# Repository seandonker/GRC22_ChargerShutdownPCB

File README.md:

# GRC22 Charging Shutdown Board for Guelph's FSAE Club
This board lies inside the external charging enclosure and is responsible for processing certain safety signals.
It then determines if it is safe to activate the battery charger or not. 

**Schematic Theory**<br>
The board takes in three main safety signals: IMD Error, AMS Safety, and Charger Safety. IMD Error indicates the insulation in between the cells of the battery pack 
and the signal faults low when an error is detected. AMS Safety faults low as well when there is an issue with the voltage/temperature/current of any individual cell bank in the battery. Finally, 
charger safety sinks current when no error is present and is allowed to float when an error occurs. The latching logic is the core design challenge of this board. 
The FSAE rulebook has specific descriptions relating to the IMD and AMS signals as once an error is noticed, the output of the board must stay in the error state until 
manually reset (power cycled). This is why latches are required to save the error state. Two RS latches were implemented in combination with RC filters, AND gates, and inverters.
This was done to combat unknown input signal conditions on startup. A full input/output-state circuit trace can be seen in the provided files (ShutdownBoard_Latching_Logic_States).
The relay logic section acts as a chain of switches, so only if  the charge sink, IMD, AMS, E-stop, and interconnect states are all correct, will then the charger and accessories be provided power.

**Board Layout**<br>
The main requirement for the PCB layout was to be able to manufacture on a two layer PCB for cost reasons. The criteria for design were ease of assembly, connector and fuse access,
and the visibility of the indicator LEDs and silkscreen.

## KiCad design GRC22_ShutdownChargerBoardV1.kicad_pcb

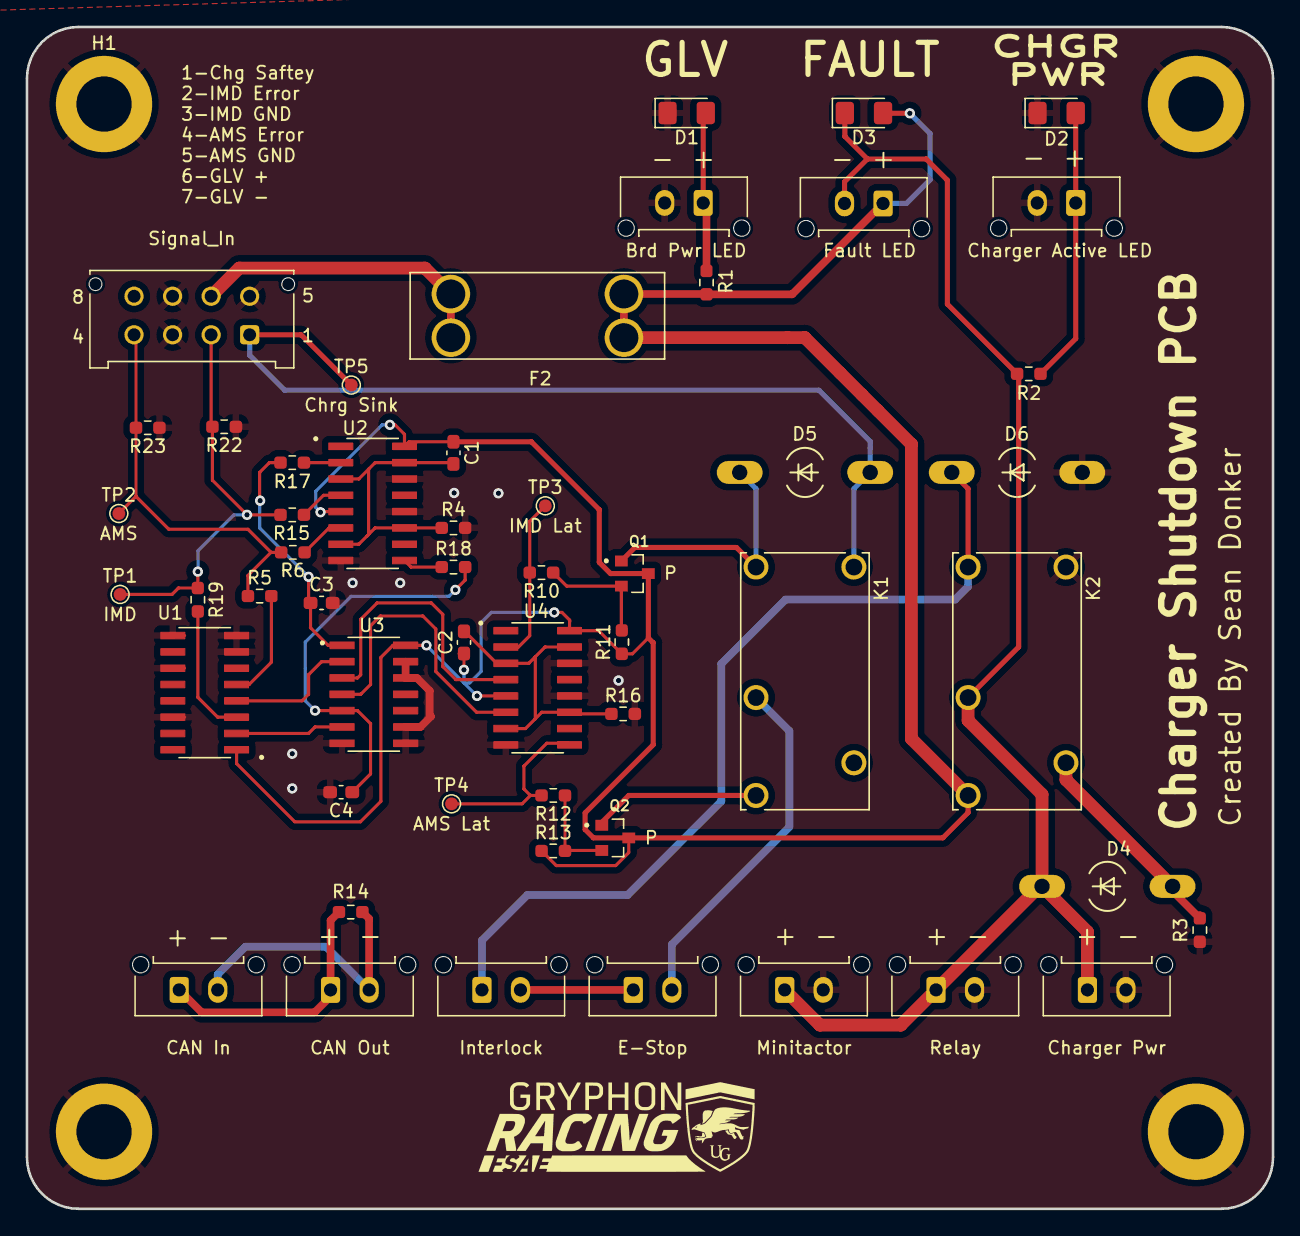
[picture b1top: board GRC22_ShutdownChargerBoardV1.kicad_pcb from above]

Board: 2 copper layers, 97.0 x 92.0 mm, 57 parts (0 on the bottom side), 35 nets.

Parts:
C1, C2: 100nF; C_0603_1608Metric_Pad1.08x0.95mm_HandSolder
C3, C4: .47nF; C_0603_1608Metric_Pad1.08x0.95mm_HandSolder
D1, D2, D3: LED; LED_1206_3216Metric_Pad1.42x1.75mm_HandSolder
D4, D5, D6: D; SOD57-10
F2: Fuse; FUSE_3557-2
H1, H2, H3, H4: M4_Hole; MountingHole_4.3mm_M4_DIN965_Pad
J1: Signal_In; Molex_Micro-Fit_3.0_43045-0812_2x04_P3.00mm_Vertical
J2: Charger Pwr; Molex_Micro-Fit_3.0_43650-0215_1x02_P3.00mm_Vertical
J3: Relay; Molex_Micro-Fit_3.0_43650-0215_1x02_P3.00mm_Vertical
J4: Minitactor; Molex_Micro-Fit_3.0_43650-0215_1x02_P3.00mm_Vertical
J5: Interlock; Molex_Micro-Fit_3.0_43650-0215_1x02_P3.00mm_Vertical
J6: E-Stop; Molex_Micro-Fit_3.0_43650-0215_1x02_P3.00mm_Vertical
J7: CAN In; Molex_Micro-Fit_3.0_43650-0215_1x02_P3.00mm_Vertical
J8: CAN Out; Molex_Micro-Fit_3.0_43650-0215_1x02_P3.00mm_Vertical
J9: Brd Pwr LED; Molex_Micro-Fit_3.0_43650-0215_1x02_P3.00mm_Vertical
J10: Charger Active LED; Molex_Micro-Fit_3.0_43650-0215_1x02_P3.00mm_Vertical
J11: Fault LED; Molex_Micro-Fit_3.0_43650-0215_1x02_P3.00mm_Vertical
K1, K2: ALQ112; RELAY_ALQ112
Q1, Q2: PMOS; RSC002
R1, R2, R3, R5, R6, R10, R12, R15, R19: 470; R_0603_1608Metric_Pad0.98x0.95mm_HandSolder
R4, R16: 1K; R_0603_1608Metric_Pad0.98x0.95mm_HandSolder
R11, R13: 100k; R_0603_1608Metric_Pad0.98x0.95mm_HandSolder
R14: 120; R_0603_1608Metric_Pad0.98x0.95mm_HandSolder
R17, R18: 10k; R_0603_1608Metric_Pad0.98x0.95mm_HandSolder
R22, R23: 2.2K; R_0603_1608Metric_Pad0.98x0.95mm_HandSolder
TP1: IMD; TestPoint_Pad_D1.0mm
TP2: AMS; TestPoint_Pad_D1.0mm
TP3: IMD Lat; TestPoint_Pad_D1.0mm
TP4: AMS Lat; TestPoint_Pad_D1.0mm
TP5: Chrg Sink; TestPoint_Pad_D1.0mm
U1: SOIC127P600X175-16N
U2, U4: MC14043BDG; SOIC127P600X175-16N
U3: MC14081BDG; SOIC127P600X175-14N

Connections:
+12V: C1.1, C2.1, D3.2 (A), F2.2, J11.1, K2.5, Q1.3 (S), Q2.3 (S), R1.1, R11.1, R13.1, U1.1 (VDD), U2.5 (E), U2.16 (VDD), U3.14 (VDD), U4.5 (E), U4.16 (VDD)
AMS GND: C3.2, C4.2, D1.1 (K), D2.1 (K), D6.2 (A), H1.1, H2.1, H3.1, H4.1, J1.3, J1.5, J1.7, J2.2, J3.2, J4.2, J9.2, J10.2, K2.2, R3.2, R4.2, R16.2, R22.1, R23.1, U1.7 (IN_c), U1.8 (VSS), U1.9 (IN_d), U1.11 (IN_e), U1.14 (IN_f), U2.8 (VSS), U2.12 (S2), U2.14 (S3), U3.7 (VSS), U3.8 (IN_1C), U3.9 (IN_2C), U3.12 (IN_1D), U3.13 (IN_2D), U4.8 (VSS), U4.12 (S2), U4.14 (S3)
AMS Saftey: J1.4, R5.1, R6.1, R23.2, TP2.1
AMS_Latched: R12.2, TP4.1, U4.9 (Q1)
CAN +: J7.1, J8.1, R14.2
CAN -: J7.2, J8.2, R14.1
Charger Pwr: D3.1 (K), D4.1 (K), J2.1, J3.1, J4.1, J11.2, K2.3, R2.1
Chg Saftey: D5.2 (A), J1.1, K1.2, TP5.1
E-Stop Out: J6.2, K1.3
E-Stop Rtn: J5.2, J6.1
GLV +: F2.1, J1.6
IMD Error: J1.2, R15.1, R19.1, R22.2, TP1.1
IMD_Latched: R10.2, TP3.1, U4.2 (Q0)
Interlock Rtn: D6.1 (K), J5.1, K2.1
unnamed: D1.2 (A), J9.1, R1.2
unnamed: D2.2 (A), J10.1, R2.2
unnamed: D4.2 (A), K2.4, R3.1
unnamed: D5.1 (K), K1.1, Q1.1 (D)
unnamed: Q1.2 (G), R10.1, R11.2
unnamed: K1.5, Q2.1 (D)
unnamed: Q2.2 (G), R12.1, R13.2
unnamed: R19.2, U1.3 (IN_a)
unnamed: R5.2, U1.5 (IN_b)
unnamed: U1.2 (OUT_a), U3.6 (IN_2B)
unnamed: U1.4 (OUT_b), U3.2 (IN_2A)
unnamed: R17.1, U2.2 (Q0)
unnamed: R18.1, U2.9 (Q1)
unnamed: C1.2, R4.1, U2.3 (R0), U2.7 (R1), U2.11 (R2), U2.15 (R3)
unnamed: R15.2, U2.4 (S0)
unnamed: R6.2, U2.6 (S1)
unnamed: C3.1, R17.2, U3.1 (IN_1A)
unnamed: C4.1, R18.2, U3.5 (IN_1B)
unnamed: U3.3 (OUTA), U4.4 (S0)
unnamed: U3.4 (OUTB), U4.6 (S1)
unnamed: C2.2, R16.1, U4.3 (R0), U4.7 (R1), U4.11 (R2), U4.15 (R3)

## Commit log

2023-11-27 First file upload
2023-11-27 Added folders
2023-11-27 Created README.md
